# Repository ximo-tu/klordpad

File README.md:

# Klordpad
Klordpad is a 6 key macropad with a rotary encoder and an OLED Dislay! 

It is built for faster git commands, keyboard shortcuts and enhanced gaming

## Features:
- Dual Layer acrylic case
- 128x32 OLED Display
- EC11 ROtary encoder for modes
- 6 keys

CAD Model: everything fits together using 5 M3 Bolts and heatset inserts. 4 for the case, one for the PCB. 

It has 2 separate printed pieces: The base and the top. 

PCB:

Here's my PCB made in KiCad:

Schematic

PCB

## Firmware Overview

This hackpad uses python for firmware.

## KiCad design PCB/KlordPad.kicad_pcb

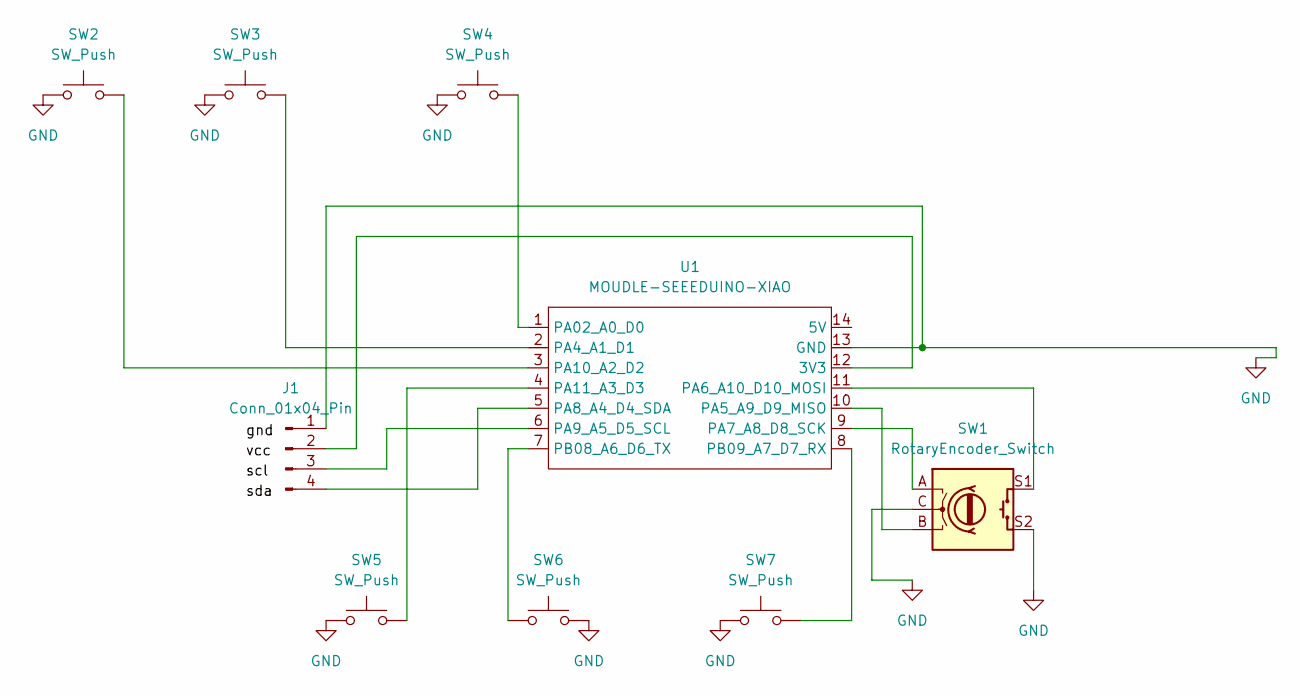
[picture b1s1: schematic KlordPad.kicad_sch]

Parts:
J1: Conn_01x04_Pin; PinHeader_1x04_P2.54mm_Vertical
SW1: RotaryEncoder_Switch; RotaryEncoder_Alps_EC11E-Switch_Vertical_H20mm
SW2, SW3, SW4, SW5, SW6, SW7: SW_Push; SW_Cherry_MX_1.00u_PCB
U1: MOUDLE-SEEEDUINO-XIAO; XIAO-Generic-Hybrid-14P-2.54-21X17.8MM

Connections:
GND: J1.1, SW1.C, SW1.S2, SW2.1, SW3.1, SW4.1, SW5.1, SW6.2, SW7.1, U1.13 (GND)
unnamed: J1.2, U1.12 (3V3)
unnamed: J1.3, U1.6 (PA9_A5_D5_SCL)
unnamed: J1.4, U1.5 (PA8_A4_D4_SDA)
unnamed: SW4.2, U1.1 (PA02_A0_D0)
unnamed: SW3.2, U1.2 (PA4_A1_D1)
unnamed: SW1.B, U1.10 (PA5_A9_D9_MISO)
unnamed: SW1.S1, U1.11 (PA6_A10_D10_MOSI)
unnamed: SW1.A, U1.9 (PA7_A8_D8_SCK)
unnamed: SW2.2, U1.3 (PA10_A2_D2)
unnamed: SW5.2, U1.4 (PA11_A3_D3)
unnamed: SW6.1, U1.7 (PB08_A6_D6_TX)
unnamed: SW7.2, U1.8 (PB09_A7_D7_RX)

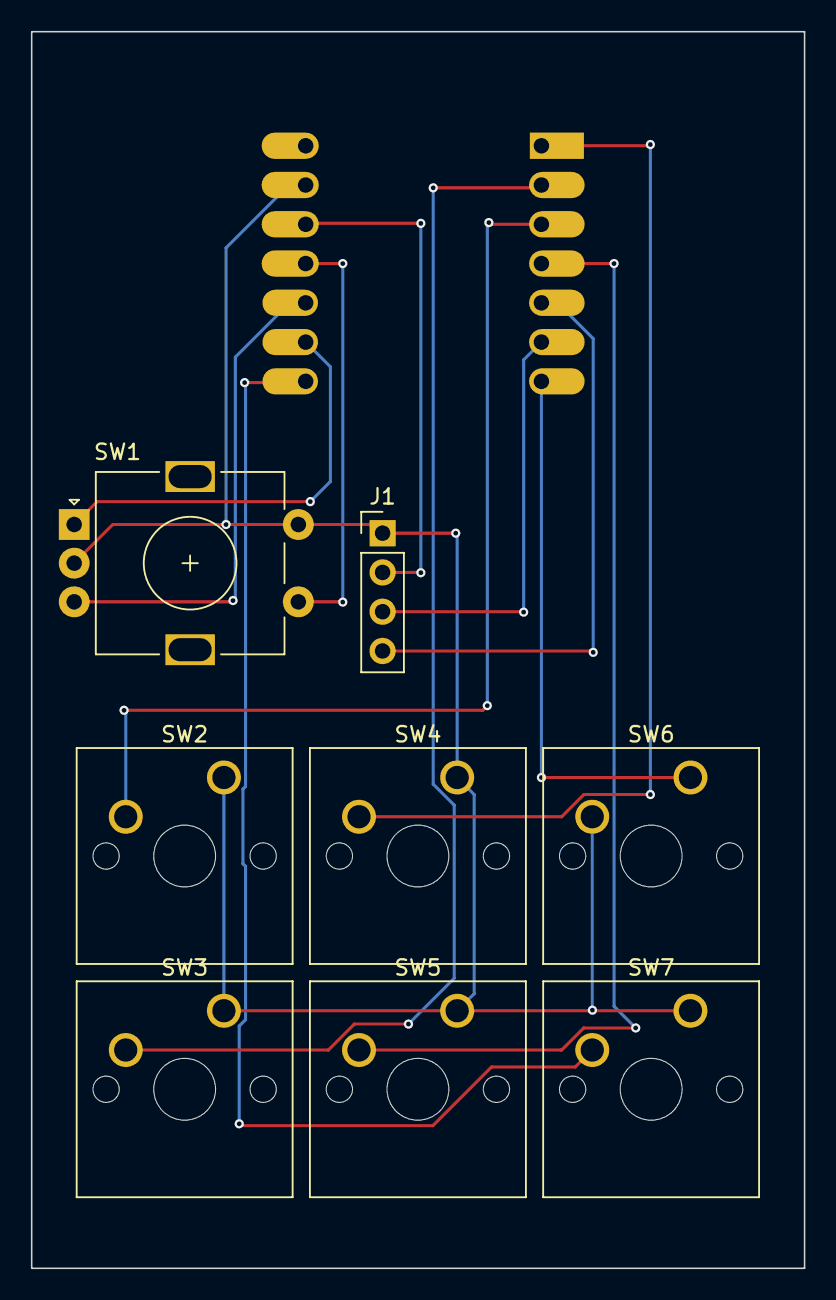
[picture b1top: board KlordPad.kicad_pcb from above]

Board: 2 copper layers, 50.0 x 80.0 mm, 9 parts (1 on the bottom side), 13 nets.

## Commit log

2026-06-17 project except main.py and readme and gerbers
2026-06-18 FIRMWARE
